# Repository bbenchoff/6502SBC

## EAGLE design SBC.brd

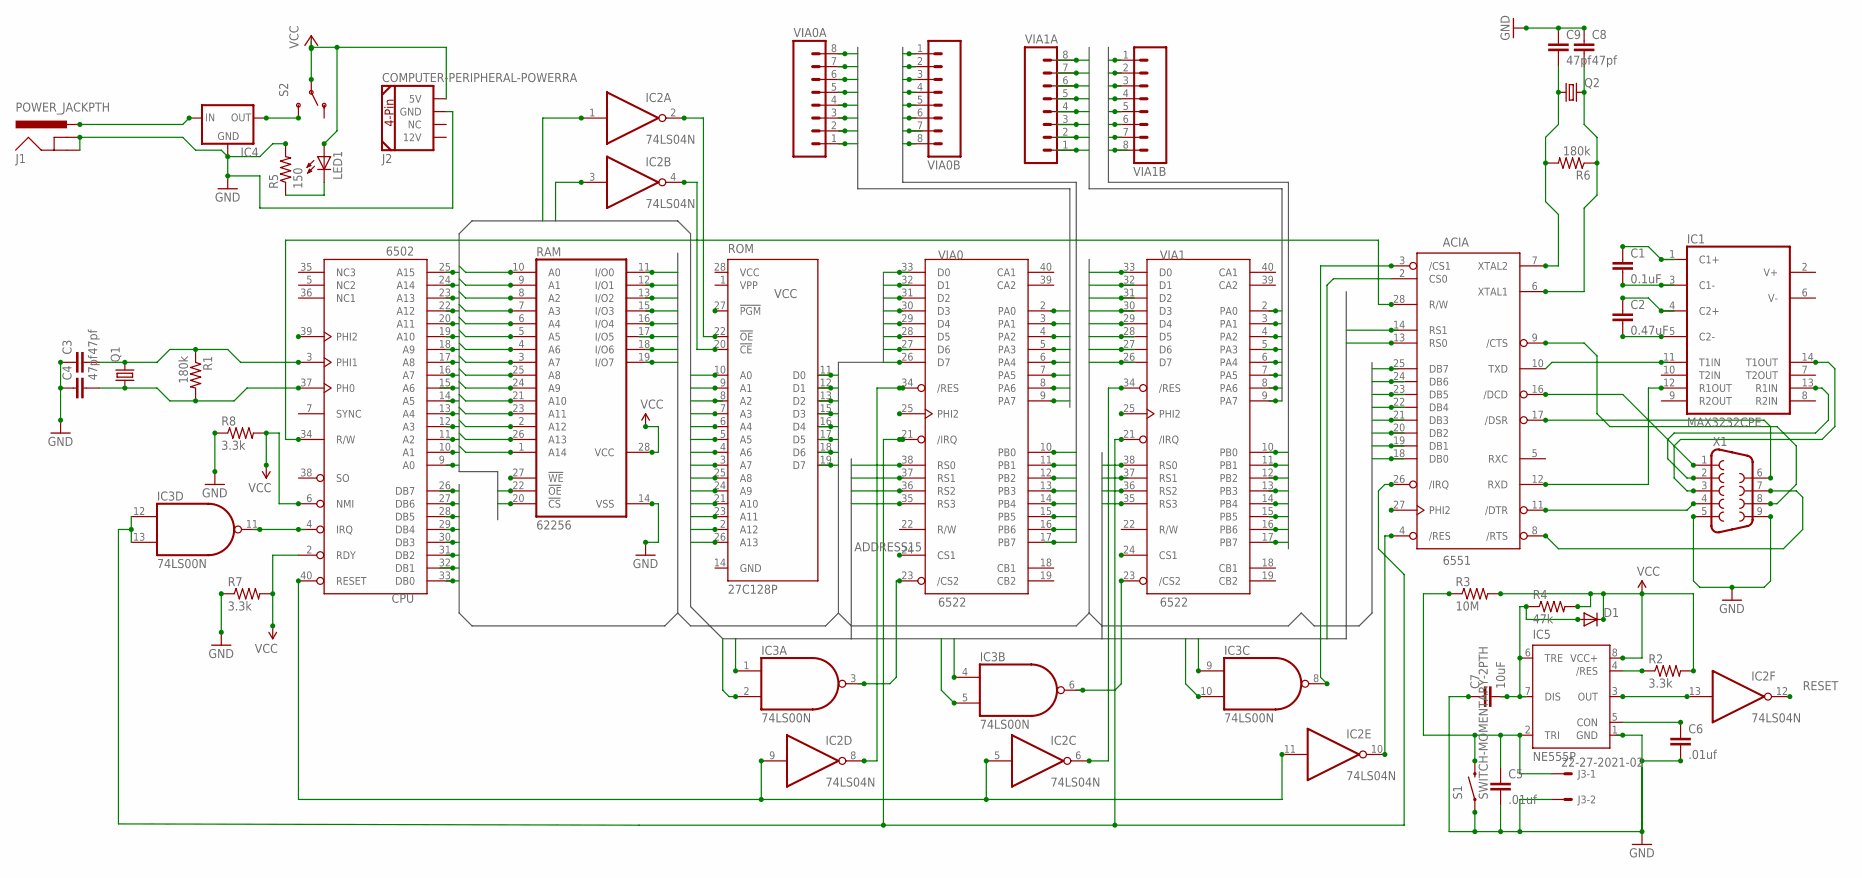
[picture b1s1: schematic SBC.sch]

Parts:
ACIA: 6551; DIP28
C1: 0.1uF; CAP-PTH-SMALL-KIT
C2: 0.47uF; CAP-PTH-SMALL-KIT
C3, C4, C8, C9: 47pf; CAP-PTH-SMALLEZ
C5, C6: .01uf; CAP-PTH-SMALLEZ
C7: 10uF; CAP-PTH-SMALLEZ
CPU: 6502; DIP40
D1: DIODE1N4148; DIODE-1N4148
IC1: MAX3232CPE; DIL16
IC2: 74LS04N; DIL14
IC3: 74LS00N; DIL14
IC4: V_REG_78XX-TO-220; TO-220-ALT
IC5: NE555P; DIL-08
J1: POWER_JACKPTH; POWER_JACK_PTH
J2: COMPUTER-PERIPHERAL-POWERRA; COMPUTER-PERIPHERAL-POWER-RA
J3: 22-27-2021-02; 6410-02
LED1: LED3MM
Q1, Q2: CRYSTALHC49S; HC49/S
R1, R6: 180k; AXIAL-0.3EZ
R2: 3.3k; AXIAL-0.3
R3: 10M; AXIAL-0.3
R4: 47k; AXIAL-0.3
R5: 150; AXIAL-0.3EZ
R7, R8: 3.3k; AXIAL-0.3EZ
RAM: 62256; DIL28-6
ROM: 27C128P; DIL28-6
S1: SWITCH-MOMENTARY-2PTH; TACTILE-PTH
S2: SWITCH-SPDTPTH_LOCK; SWITCH-SPDT_LOCK.007S
VIA0, VIA1: 6522; DIP40
VIA0A, VIA0B, VIA1A, VIA1B: M08LONGPADS; 1X08_LONGPADS
X1: DB9FEMALE; DB9

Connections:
65IRQ: CPU.4 (IRQ), IC3.11 (O)
ADDRESS0: ACIA.13 (RS0), CPU.9 (A0), RAM.10 (A0), ROM.10 (A0), VIA0.38 (RS0), VIA1.38 (RS0)
ADDRESS1: ACIA.14 (RS1), CPU.10 (A1), RAM.9 (A1), ROM.9 (A1), VIA0.37 (RS1), VIA1.37 (RS1)
ADDRESS2: CPU.11 (A2), RAM.8 (A2), ROM.8 (A2), VIA0.36 (RS2), VIA1.36 (RS2)
ADDRESS3: CPU.12 (A3), RAM.7 (A3), ROM.7 (A3), VIA0.35 (RS3), VIA1.35 (RS3)
ADDRESS4: CPU.13 (A4), RAM.6 (A4), ROM.6 (A4)
ADDRESS5: CPU.14 (A5), RAM.5 (A5), ROM.5 (A5)
ADDRESS6: CPU.15 (A6), RAM.4 (A6), ROM.4 (A6)
ADDRESS7: CPU.16 (A7), RAM.3 (A7), ROM.3 (A7)
ADDRESS8: CPU.17 (A8), RAM.25 (A8), ROM.25 (A8)
ADDRESS9: CPU.18 (A9), IC3.10 (I1), RAM.24 (A9), ROM.24 (A9)
ADDRESS10: CPU.19 (A10), IC3.5 (I1), RAM.21 (A10), ROM.21 (A10)
ADDRESS11: CPU.20 (A11), IC3.2 (I1), RAM.23 (A11), ROM.23 (A11)
ADDRESS12: CPU.22 (A12), IC3.1 (I0), IC3.4 (I0), IC3.9 (I0), RAM.2 (A12), ROM.2 (A12)
ADDRESS13: CPU.23 (A13), IC2.1 (I), RAM.26 (A13), ROM.26 (A13)
ADDRESS14: CPU.24 (A14), RAM.1 (A14)
ADDRESS15: ACIA.2 (CS0), CPU.25 (A15), IC2.3 (I), RAM.20 (!CS), RAM.22 (!OE), VIA0.24 (CS1), VIA1.24 (CS1)
CLEARTOSEND: ACIA.9 (/CTS), X1.8
DATA0: ACIA.18 (DB0), CPU.33 (DB0), RAM.11 (I/O0), ROM.11 (D0), VIA0.33 (D0), VIA1.33 (D0)
DATA1: ACIA.19 (DB1), CPU.32 (DB1), RAM.12 (I/O1), ROM.12 (D1), VIA0.32 (D1), VIA1.32 (D1)
DATA2: ACIA.20 (DB2), CPU.31 (DB2), RAM.13 (I/O2), ROM.13 (D2), VIA0.31 (D2), VIA1.31 (D2)
DATA3: ACIA.21 (DB3), CPU.30 (DB3), RAM.15 (I/O3), ROM.15 (D3), VIA0.30 (D3), VIA1.30 (D3)
DATA4: ACIA.22 (DB4), CPU.29 (DB4), RAM.16 (I/O4), ROM.16 (D4), VIA0.29 (D4), VIA1.29 (D4)
DATA5: ACIA.23 (DB5), CPU.28 (DB5), RAM.17 (I/O5), ROM.17 (D5), VIA0.28 (D5), VIA1.28 (D5)
DATA6: ACIA.24 (DB6), CPU.27 (DB6), RAM.18 (I/O6), ROM.18 (D6), VIA0.27 (D6), VIA1.27 (D6)
DATA7: ACIA.25 (DB7), CPU.26 (DB7), RAM.19 (I/O7), ROM.19 (D7), VIA0.26 (D7), VIA1.26 (D7)
DATACARRIERDETECT: ACIA.16 (/DCD), X1.1
DATASETREADY: ACIA.17 (/DSR), X1.6
DTEREADY: ACIA.11 (/DTR), X1.4
GND: ACIA.1 (GND), C3.1, C4.1, C5.2, C6.2, C7.1, C8.1, C9.1, CPU.1 (GND), CPU.21 (GND), IC1.15 (GND), IC2.7 (GND), IC3.7 (GND), IC4.GND, IC5.1 (GND), J1.GND, J1.GNDBREAK, J2.GND, J3.2, R5.P$2 (2), R7.P$1 (1), R8.P$1 (1), RAM.14 (VSS), ROM.14 (GND), S1.1, VIA0.1 (GND), VIA1.1 (GND), X1.5, X1.9
IRQ: ACIA.26 (/IRQ), IC3.12 (I0), IC3.13 (I1), VIA0.21 (/IRQ), VIA1.21 (/IRQ)
unnamed: LED1.K (C), R5.P$1 (1)
unnamed: C3.2, CPU.3 (PHI1), Q1.2, R1.P$1 (1)
unnamed: IC1.14 (T1OUT), X1.3
unnamed: ACIA.28 (R/W), CPU.34 (R/W)
unnamed: C5.1, IC5.2 (TRI), J3.1, R3.P$1 (1), S1.3 (2)
unnamed: ACIA.10 (TXD), IC1.11 (T1IN)
unnamed: ACIA.12 (RXD), IC1.12 (R1OUT)
unnamed: C1.2, IC1.3 (C1-)
unnamed: C1.1, IC1.1 (C1+)
unnamed: C2.2, IC1.5 (C2-)
unnamed: C2.1, IC1.4 (C2+)
unnamed: IC2.4 (O), ROM.20 (!CE)
unnamed: IC2.2 (O), ROM.22 (!OE)
unnamed: IC3.6 (O), VIA1.23 (/CS2)
unnamed: ACIA.3 (/CS1), IC3.8 (O)
unnamed: IC3.3 (O), VIA0.23 (/CS2)
unnamed: C4.2, CPU.37 (PH0), Q1.1, R1.P$2 (2)
unnamed: C6.1, IC5.5 (CON)
unnamed: IC4.IN, J1.PWR
unnamed: IC2.8 (O), VIA0.34 (/RES)
unnamed: C7.2, D1.A, IC5.6 (TRE), IC5.7 (DIS), R4.P$1 (1)
unnamed: IC5.4 (/RES), R2.P$1 (1)
unnamed: IC2.6 (O), VIA1.34 (/RES)
unnamed: ACIA.4 (/RES), IC2.10 (O)
unnamed: IC2.13 (I), IC5.3 (OUT)
unnamed: ACIA.6 (XTAL1), C8.2, Q2.2, R6.P$1 (1)
unnamed: ACIA.7 (XTAL2), C9.2, Q2.1, R6.P$2 (2)
unnamed: IC4.OUT, S2.3 (S)
PHI2: ACIA.27 (PHI2), CPU.39 (PHI2), RAM.27 (!WE), VIA0.25 (PHI2), VIA1.25 (PHI2)
RECEIVEDATA: IC1.13 (R1IN), X1.2
REQUESTTOSEND: ACIA.8 (/RTS), X1.7
RESET: CPU.40 (RESET), IC2.5 (I), IC2.9 (I), IC2.11 (I), IC2.12 (O)
VCC: ACIA.15 (VCC), CPU.2 (RDY), CPU.6 (NMI), CPU.8 (VCC), D1.C, IC1.16 (VCC), IC2.14 (VCC), IC3.14 (VCC), IC5.8 (VCC+), J2.5V, LED1.A, R2.P$2 (2), R3.P$2 (2), R4.P$2 (2), R7.P$2 (2), R8.P$2 (2), RAM.28 (VCC), ROM.27 (!PGM), ROM.28 (VCC), S2.2, VIA0.20 (VCC), VIA1.20 (VCC)
VIA0A0: VIA0.2 (PA0), VIA0A.1
VIA0A1: VIA0.3 (PA1), VIA0A.2
VIA0A2: VIA0.4 (PA2), VIA0A.3
VIA0A3: VIA0.5 (PA3), VIA0A.4
VIA0A4: VIA0.6 (PA4), VIA0A.5
VIA0A5: VIA0.7 (PA5), VIA0A.6
VIA0A6: VIA0.8 (PA6), VIA0A.7
VIA0A7: VIA0.9 (PA7), VIA0A.8
VIA0B0: VIA0.10 (PB0), VIA0B.1
VIA0B1: VIA0.11 (PB1), VIA0B.2
VIA0B2: VIA0.12 (PB2), VIA0B.3
VIA0B3: VIA0.13 (PB3), VIA0B.4
VIA0B4: VIA0.14 (PB4), VIA0B.5
VIA0B5: VIA0.15 (PB5), VIA0B.6
VIA0B6: VIA0.16 (PB6), VIA0B.7
VIA0B7: VIA0.17 (PB7), VIA0B.8
VIA1A0: VIA1.2 (PA0), VIA1A.1
VIA1A1: VIA1.3 (PA1), VIA1A.2
VIA1A2: VIA1.4 (PA2), VIA1A.3
VIA1A3: VIA1.5 (PA3), VIA1A.4
VIA1A4: VIA1.6 (PA4), VIA1A.5
VIA1A5: VIA1.7 (PA5), VIA1A.6
VIA1A6: VIA1.8 (PA6), VIA1A.7
VIA1A7: VIA1.9 (PA7), VIA1A.8
VIA1B0: VIA1.10 (PB0), VIA1B.1
VIA1B1: VIA1.11 (PB1), VIA1B.2
VIA1B2: VIA1.12 (PB2), VIA1B.3
VIA1B3: VIA1.13 (PB3), VIA1B.4
VIA1B4: VIA1.14 (PB4), VIA1B.5
VIA1B5: VIA1.15 (PB5), VIA1B.6
VIA1B6: VIA1.16 (PB6), VIA1B.7
VIA1B7: VIA1.17 (PB7), VIA1B.8

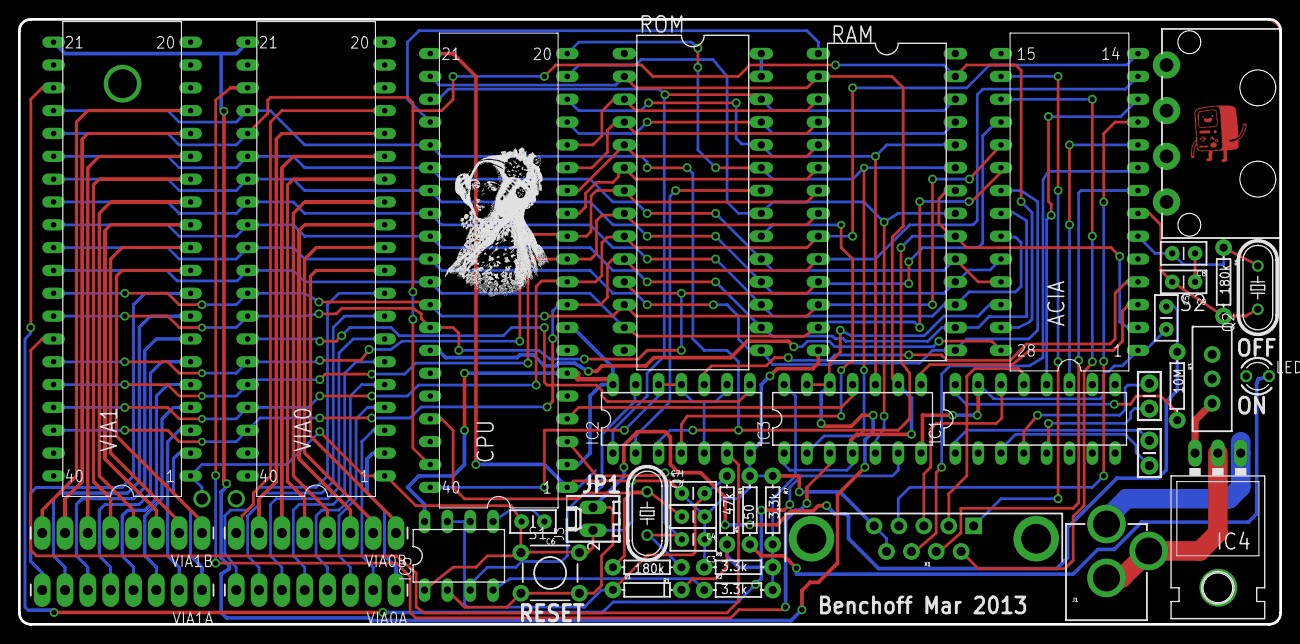
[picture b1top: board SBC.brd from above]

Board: 2 copper layers, 140.3 x 67.3 mm, 42 parts (0 on the bottom side), 96 nets.

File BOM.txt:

Part  Value                       Device                      Package                      Description
-------------------------------------------------------------------------------------------------------------------------------------------------
                                           
ACIA  6551                        6551                        DIP28                        ACIA. Capable of RS-232
CPU   6502                        6502                        DIP40                        6502 processor
VIA1  6522                        6522                        DIP40                        I/O device: two 8-bits ports, handshake lines, timers.
VIA1  6522                        6522                        DIP40                        I/O device: two 8-bits ports, handshake lines, timers.
RAM   62256                       62256P                      DIL28-6                      MEMORY
ROM   27C128P                     27C128P                     DIL28-6                      CMOS EPROM
IC1   MAX3232CPE                  MAX3232CPE                  DIL16                        True RS-232 Transceivers 3.0V to 5.5V, Low-Power
IC2   74HCT04N                    74HCT04N                    DIL14                        Hex INVERTER
IC3   74HCT00N                    74HCT00N                    DIL14                        Quad 2-input NAND gate
IC4   7805                        V_REG_78XX-TO-220           TO-220-ALT                   Voltage Regulator
IC5   NE555P                      NE555P                      DIL-08                       General purpose bipolar Timer
Q1    1MHz                        CRYSTALHC49S                HC49/S                       CRYSTAL
Q2    1.8432MHz                   CRYSTALHC49S                HC49/S                       CRYSTAL

C1    0.1uF                       CAPKIT                      CAP-PTH-SMALL-KIT            Capacitor
C2    0.47uF                      CAPKIT                      CAP-PTH-SMALL-KIT            Capacitor
C3    47pf                        CAPEZ                       CAP-PTH-SMALLEZ              Capacitor
C4    47pf                        CAPEZ                       CAP-PTH-SMALLEZ              Capacitor
C5    .01uf                       CAPEZ                       CAP-PTH-SMALLEZ              Capacitor
C6    .01uf                       CAPEZ                       CAP-PTH-SMALLEZ              Capacitor
C7    10uf                        CAPEZ                       CAP-PTH-SMALLEZ              Capacitor
C8    47pf                        CAPEZ                       CAP-PTH-SMALLEZ              Capacitor
C9    47pf                        CAPEZ                       CAP-PTH-SMALLEZ              Capacitor

D1    1N4148                      DIODE1N4148                 DIODE-1N4148                 Diode
LED1  GREEN                       LED3MM                      LED3MM                       LED

R1    180k                        RESISTOREZ                  AXIAL-0.3EZ                  Resistor
R2    3.3k                        RESISTORAXIAL-0.3           AXIAL-0.3                    Resistor
R3    10M                         RESISTORAXIAL-0.3           AXIAL-0.3                    Resistor
R4    47k                         RESISTORAXIAL-0.3           AXIAL-0.3                    Resistor
R5    150                         RESISTOREZ                  AXIAL-0.3EZ                  Resistor
R6    180k                        RESISTOREZ                  AXIAL-0.3EZ                  Resistor
R7    3.3k                        RESISTOREZ                  AXIAL-0.3EZ                  Resistor
R8    3.3k                        RESISTOREZ                  AXIAL-0.3EZ                  Resistor

S1    SWITCH-MOMENTARY-2PTH       SWITCH-MOMENTARY-2PTH       TACTILE-PTH                  Various NO switches- pushbuttons, reed, etc 
S2    SWITCH-SPDT                 SWITCH-SPDT                                              SPDT Switch
J1    POWER_JACKPTH               POWER_JACKPTH               POWER_JACK_PTH               Power Jack
J2    4 pin Molex                 COMPUTER-PERIPHERAL-POWERRA COMPUTER-PERIPHERAL-POWER-RA 
X1    DE9 Female right angle      DB9FEMALE                   DB9                          DB9 Connector
J3    22-27-2021-02               22-27-2021-02               6410-02                      CONNECTOR

VIA0A                             M08LONGPADS                 1X08_LONGPADS                Header 8                                                                                                 
VIA0B                             M08LONGPADS                 1X08_LONGPADS                Header 8                                                                                                                                                   
VIA1A                             M08LONGPADS                 1X08_LONGPADS                Header 8  
VIA1B                             M08LONGPADS                 1X08_LONGPADS                Header 8

BOX   Hammond 1402DV					      Hammond 1402-series	   Enclosure
T1    Hammond 166K12              Power Transformers 12.6ct VAC / 1.2 Amp                  Transformer

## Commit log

2013-03-29 First Commit
    BOM, board, and schematic
2013-03-31 Added gerber files
2013-04-03 Fixed issue with SMD switch
    Updated schematic, board, BOM & gerbers for through-hole switch. Sent
    gerber off to production.

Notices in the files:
parts and their libraries:
SparkFun-Connectors: Licensing: CC v3.0 Share-Alike You are welcome to use this library for commercial purposes.
